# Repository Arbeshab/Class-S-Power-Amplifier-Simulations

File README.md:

Supplement material for the publication "Comprehensive Study of Class S Power Amplification Technology for High-Frequency Communications Systems"

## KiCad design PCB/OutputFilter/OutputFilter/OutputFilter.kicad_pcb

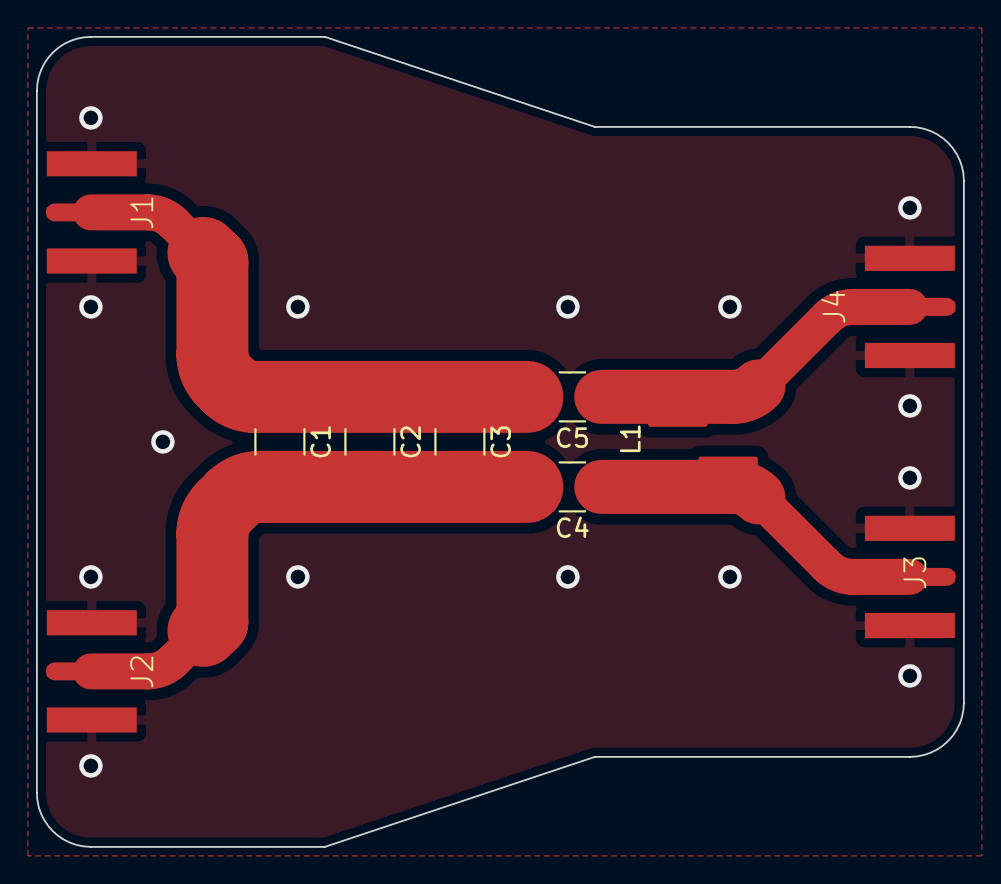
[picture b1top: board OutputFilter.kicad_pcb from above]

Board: 2 copper layers, 51.5 x 45.0 mm, 10 parts (0 on the bottom side), 5 nets.

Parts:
C1, C4, C5: 3.3e-9; C_1210_3225Metric_Pad1.33x2.70mm_HandSolder
C2: 0.1e-9; C_1210_3225Metric_Pad1.33x2.70mm_HandSolder
C3: 0; C_1210_3225Metric_Pad1.33x2.70mm_HandSolder
J1, J2, J3, J4: Conn_Coaxial; 60312202114513_corrected
L1: 12.5e-9; AxxTGL

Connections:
GND: J1.2 (Ext), J2.2 (Ext), J3.2 (Ext), J4.2 (Ext)
unnamed: C1.1, C2.1, C3.1, C5.2, J1.1 (In)
unnamed: C1.2, C2.2, C3.2, C4.2, J2.1 (In)
unnamed: C4.1, J3.1 (In), L1.1
unnamed: C5.1, J4.1 (In), L1.2

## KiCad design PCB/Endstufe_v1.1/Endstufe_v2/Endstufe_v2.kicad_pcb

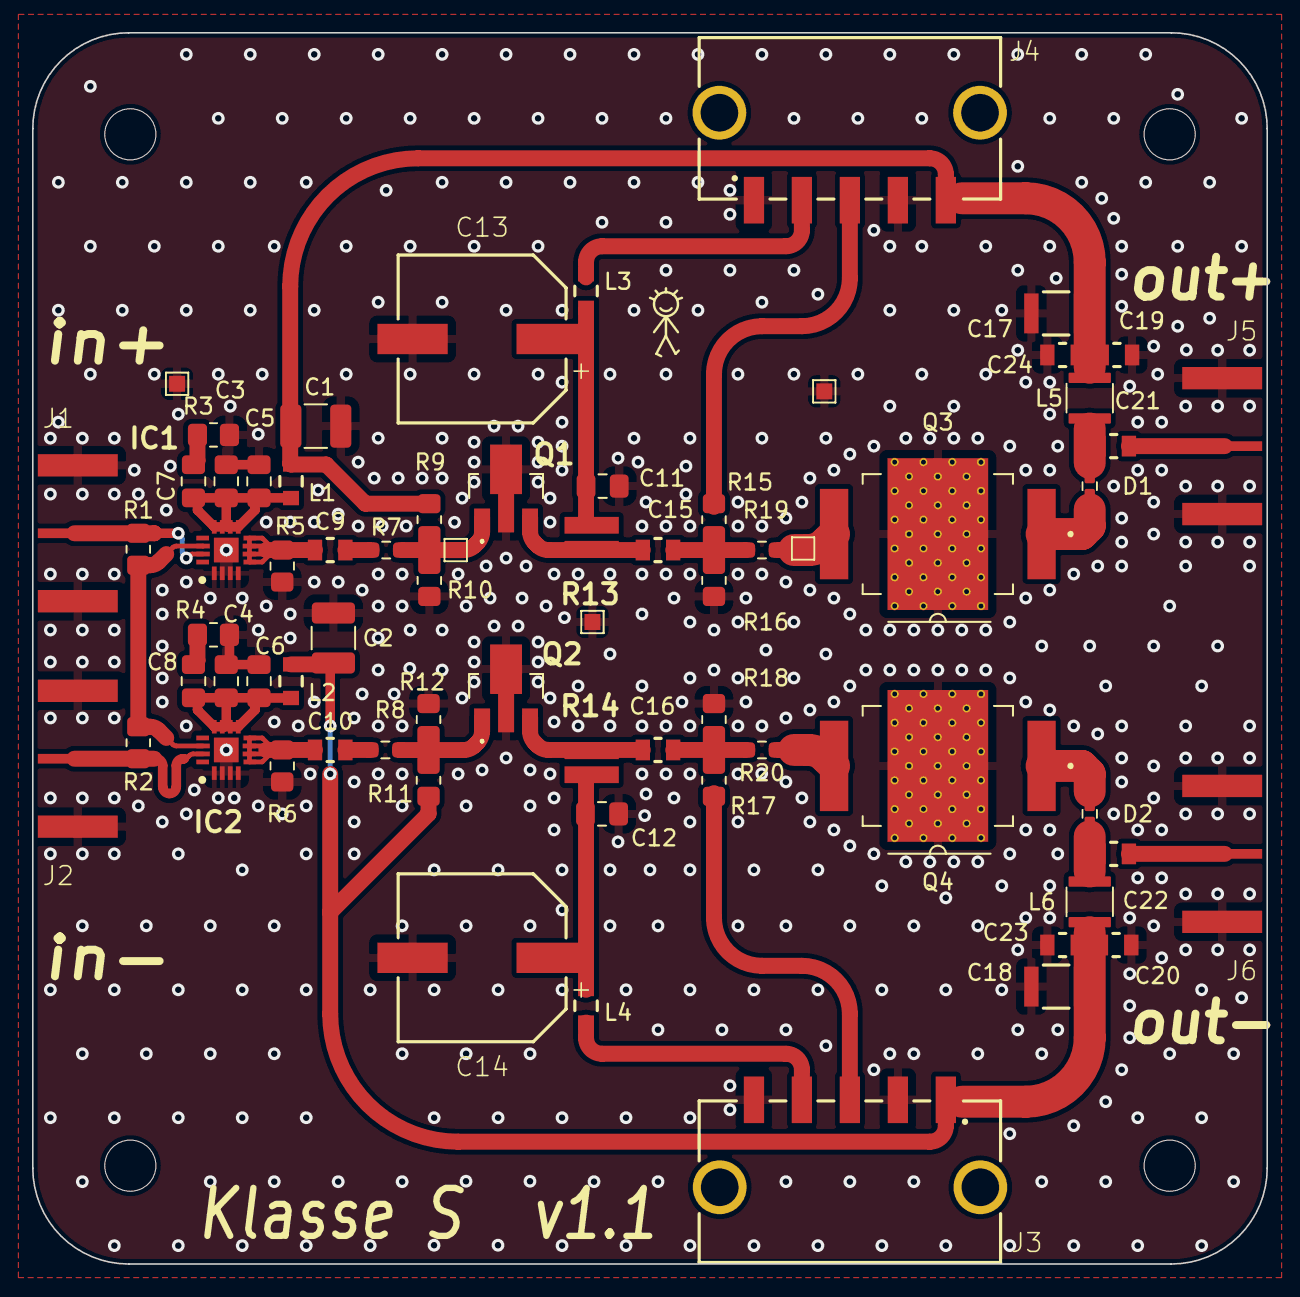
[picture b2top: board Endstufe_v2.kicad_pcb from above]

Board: 2 copper layers, 77.2 x 77.0 mm, 64 parts (0 on the bottom side), 31 nets.

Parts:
C1, C2: 22uF; C_1210_3225Metric_Pad1.33x2.70mm_HandSolder
C3, C4: 47pF; C_0805_2012Metric_Pad1.18x1.45mm_HandSolder
C5, C6: 47nF; C_0805_2012Metric_Pad1.18x1.45mm_HandSolder
C7, C8: 100nF; C_0805_2012Metric_Pad1.18x1.45mm_HandSolder
C9, C10, C15, C16, C21, C22: 1e-9; WCAP-CSGP_0805_H0.8_R
C11, C12: 885012207095_33nF; C_0805_2012Metric_Pad1.18x1.45mm_HandSolder
C13, C14: 865080657017_150uF; WCAP-ASLI_10X10.5(DXL)
C17, C18: 47e-6; WCAP-CSGP_1210_H2.5
C19, C20: 68e-9; WCAP-CSGP_0805_H0.8_R
C23, C24: 1.5e-9; WCAP-CSGP_0805_H0.8_R
D1, D2: MPP4202; mpp4202
IC1, IC2: THS4302RGTR; QFN50P300X300X100-17N-D
J1, J2: Conn_Coaxial; 1.6mmSMD_SMA_sideways
J3: powerConn5Lower; 662105130822
J4: powerConn5Upper; 662105130822
J5: outp_SMA; 1.6mmSMD_SMA_sideways
J6: outn_SMA; 1.6mmSMD_SMA_sideways
L1, L2, L3, L4: 742792036; WE-CBF_0805(W=3.0)
L5, L6: 10e-6; 1210POC
Q1, Q2: RFM01U7P_TE12L; RFM01U7PTE12LF
Q3, Q4: PD55003-E; TRANS_PD55008-E
R1, R2: 50; R_0805_2012Metric_Pad1.20x1.40mm_HandSolder
R3, R4: 30; R_0805_2012Metric_Pad1.20x1.40mm_HandSolder
R5, R6: 100; R_0805_2012Metric_Pad1.20x1.40mm_HandSolder
R7, R8: 5; R_0603_1608Metric_Pad0.98x0.95mm_HandSolder
R9, R11: 3.3k; R_0805_2012Metric_Pad1.20x1.40mm_HandSolder
R10, R12: 2.2k; R_0805_2012Metric_Pad1.20x1.40mm_HandSolder
R13, R14: 10; RESC1632X70N
R15, R17: 910; R_0805_2012Metric_Pad1.20x1.40mm_HandSolder
R16, R18: 4.7k; R_0805_2012Metric_Pad1.20x1.40mm_HandSolder
R19, R20: 1; R_0603_1608Metric_Pad0.98x0.95mm_HandSolder

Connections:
+5V: C1.2, C2.2, C17.1, C18.1, C19.1, C20.1, C23.1, C24.1, J3.1 (+5V), J4.5 (+5V), L1.2, L2.2, L5.2, L6.2, R9.2, R11.2
/V_in_N: IC2.15 (VIN+), J2.1 (In), R2.2
/V_in_P: IC1.15 (VIN+), J1.1 (In), R1.1
GND: C1.1, C2.1, C3.1, C4.1, C5.1, C6.1, C11.1, C12.1, C13.2, C14.2, C17.2, C18.2, C19.2, C20.2, C23.2, C24.2, IC1.1 (VS-_1), IC1.2 (VS-_2), IC1.3 (VS-_3), IC1.4 (VS-_4), IC1.17 (EP), IC2.1 (VS-_1), IC2.2 (VS-_2), IC2.3 (VS-_3), IC2.4 (VS-_4), IC2.17 (EP), J1.2 (Ext), J2.2 (Ext), J3.2 (GND), J3.5 (GND), J4.1 (GND), J4.4 (GND), J5.2 (Ext), J6.2 (Ext), Q1.2 (S_1), Q1.4 (S_2), Q2.2 (S_1), Q2.4 (S_2), Q3.3 (S), Q4.3 (S), R3.1, R4.1, R5.2, R6.2, R10.1, R12.1, R16.1, R18.1
unnamed: C3.2, C5.2, C7.2, IC1.9 (VS+_1), IC1.10 (VS+_2), IC1.11 (VS+_3), IC1.12 (VS+_4), L1.1
unnamed: C4.2, C6.2, C8.1, IC2.9 (VS+_1), IC2.10 (VS+_2), IC2.11 (VS+_3), IC2.12 (VS+_4), L2.1
unnamed: C7.1, R3.2
unnamed: C8.2, R4.2
unnamed: C9.1, IC1.5 (VOUT_1), IC1.6 (VOUT_2), IC1.7 (VOUT_3), IC1.8 (VOUT_4), R5.1
unnamed: C10.1, IC2.5 (VOUT_1), IC2.6 (VOUT_2), IC2.7 (VOUT_3), IC2.8 (VOUT_4), R6.1
unnamed: C11.2, C13.1, L3.2, R13.2
unnamed: C12.2, C14.1, L4.2, R14.2
unnamed: C15.1, Q1.3 (D), R13.1
unnamed: C16.1, Q2.3 (D), R14.1
unnamed: C21.1, D1.1 (A), L5.1
unnamed: C21.2, J5.1 (In)
unnamed: C22.1, D2.1 (A), L6.1
unnamed: C22.2, J6.1 (In)
unnamed: D1.2 (C), Q3.1 (D)
unnamed: D2.2 (C), Q4.1 (D)
unnamed: IC1.14 (VIN-), IC2.14 (VIN-), R1.2, R2.1
unnamed: Q1.1 (G), R7.2, R9.1, R10.2
unnamed: Q2.1 (G), R8.2, R11.1, R12.2
unnamed: Q3.2 (G), R19.1
unnamed: Q4.2 (G), R20.1
VDC: J3.3 (Vbias), J4.3 (Vbias), R15.2, R17.2
VDD: J3.4 (Vdd), J4.2 (Vdd), L3.1, L4.1
outn_stage1: C10.2, R8.1
outn_stage2: C16.2, R17.1, R18.2, R20.2
outp_stage1: C9.2, R7.1
outp_stage2: C15.2, R15.1, R16.2, R19.2
